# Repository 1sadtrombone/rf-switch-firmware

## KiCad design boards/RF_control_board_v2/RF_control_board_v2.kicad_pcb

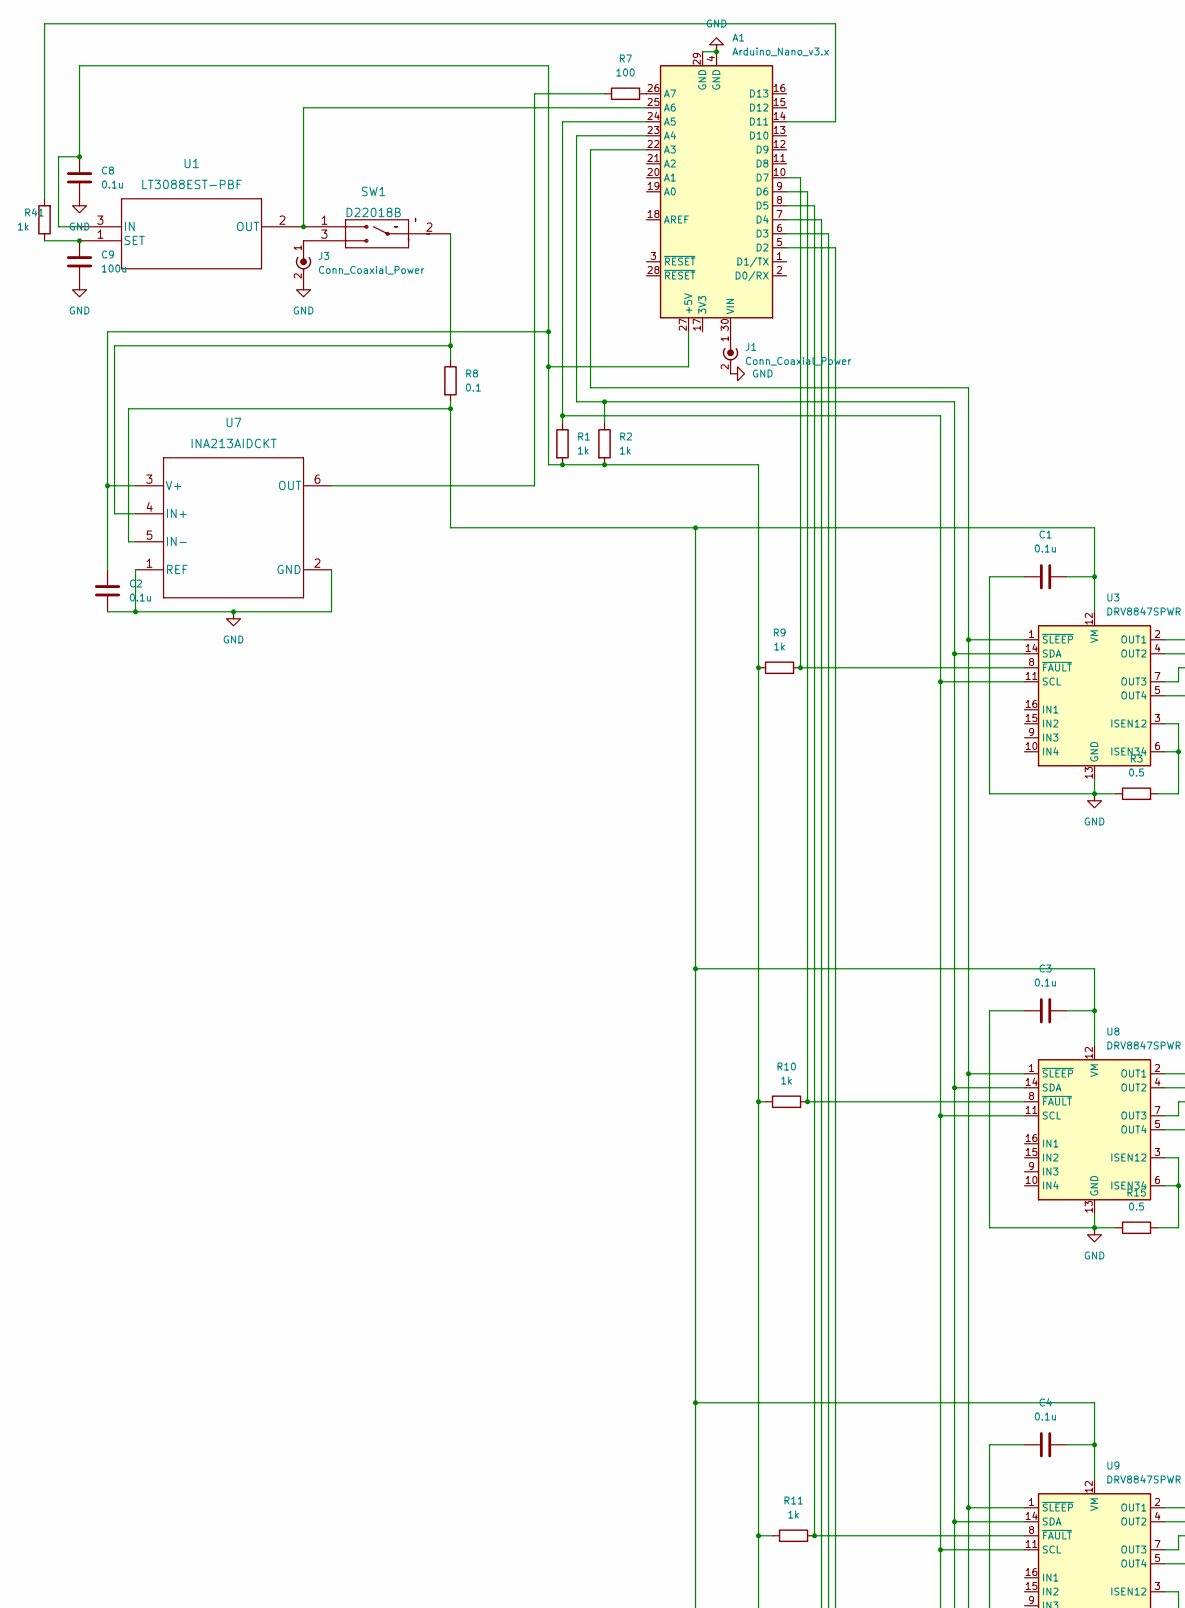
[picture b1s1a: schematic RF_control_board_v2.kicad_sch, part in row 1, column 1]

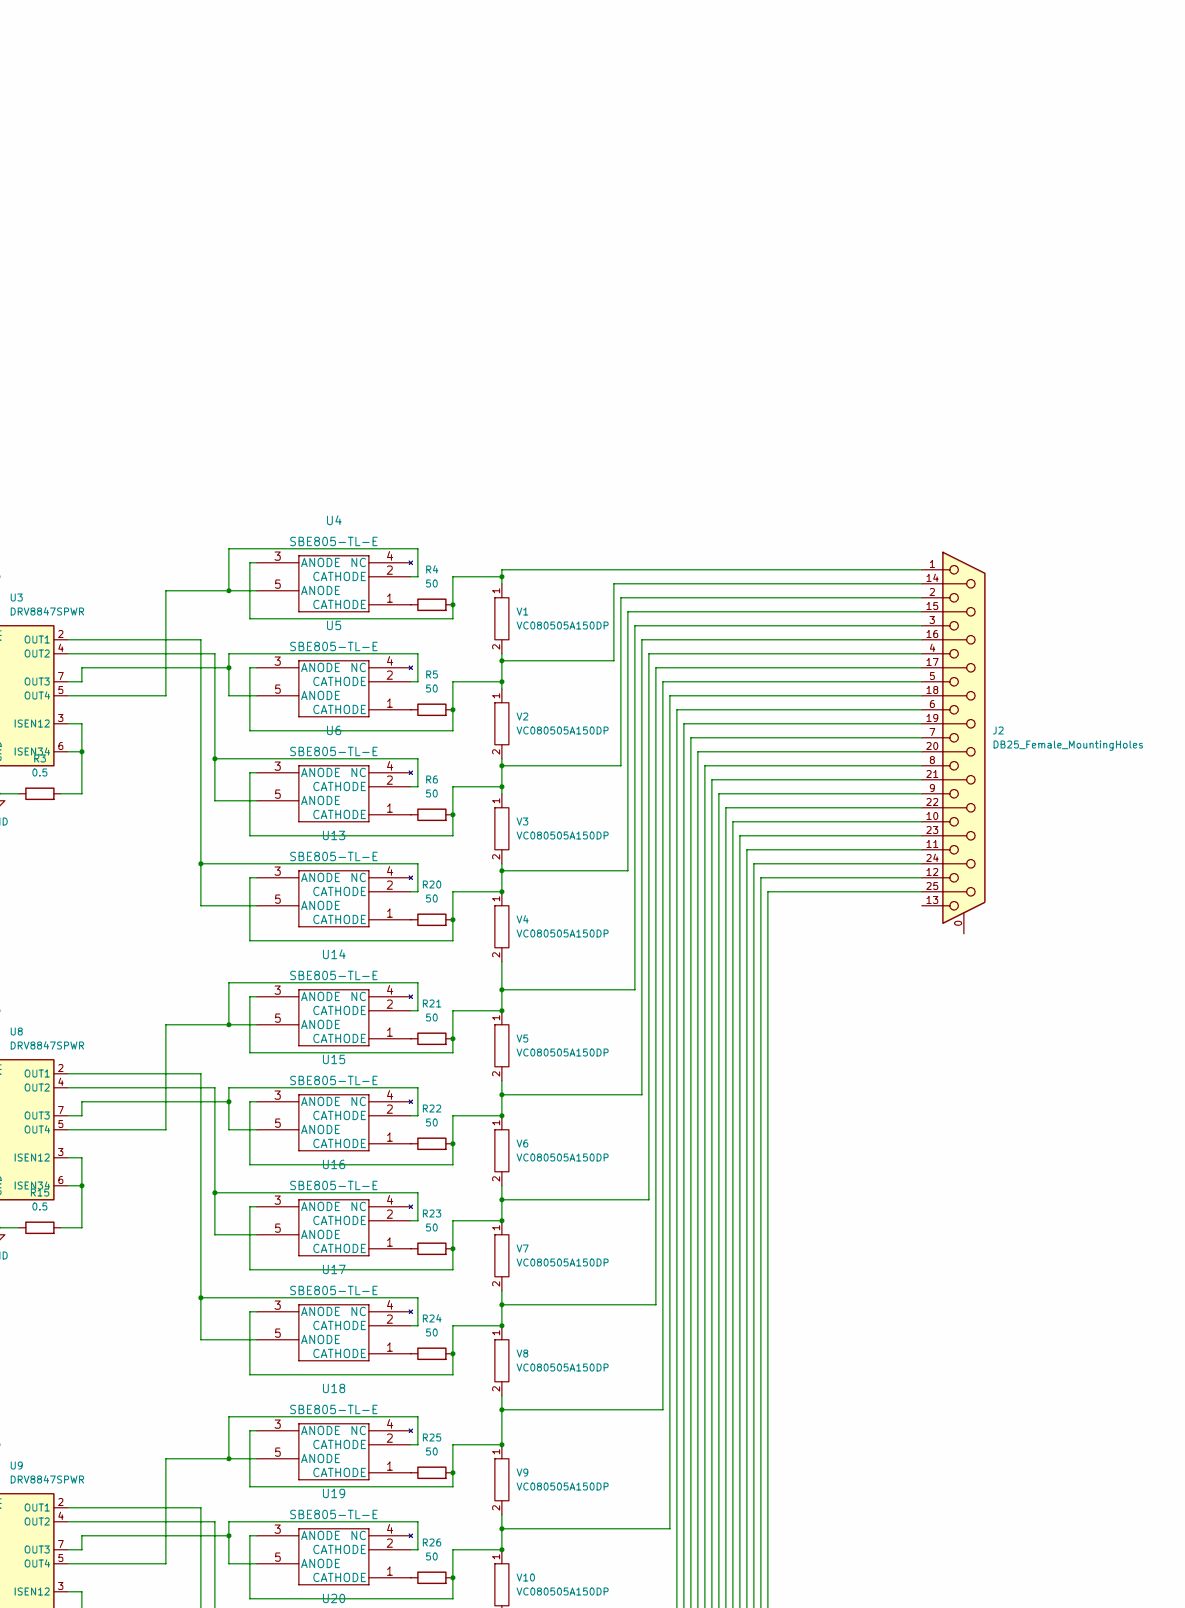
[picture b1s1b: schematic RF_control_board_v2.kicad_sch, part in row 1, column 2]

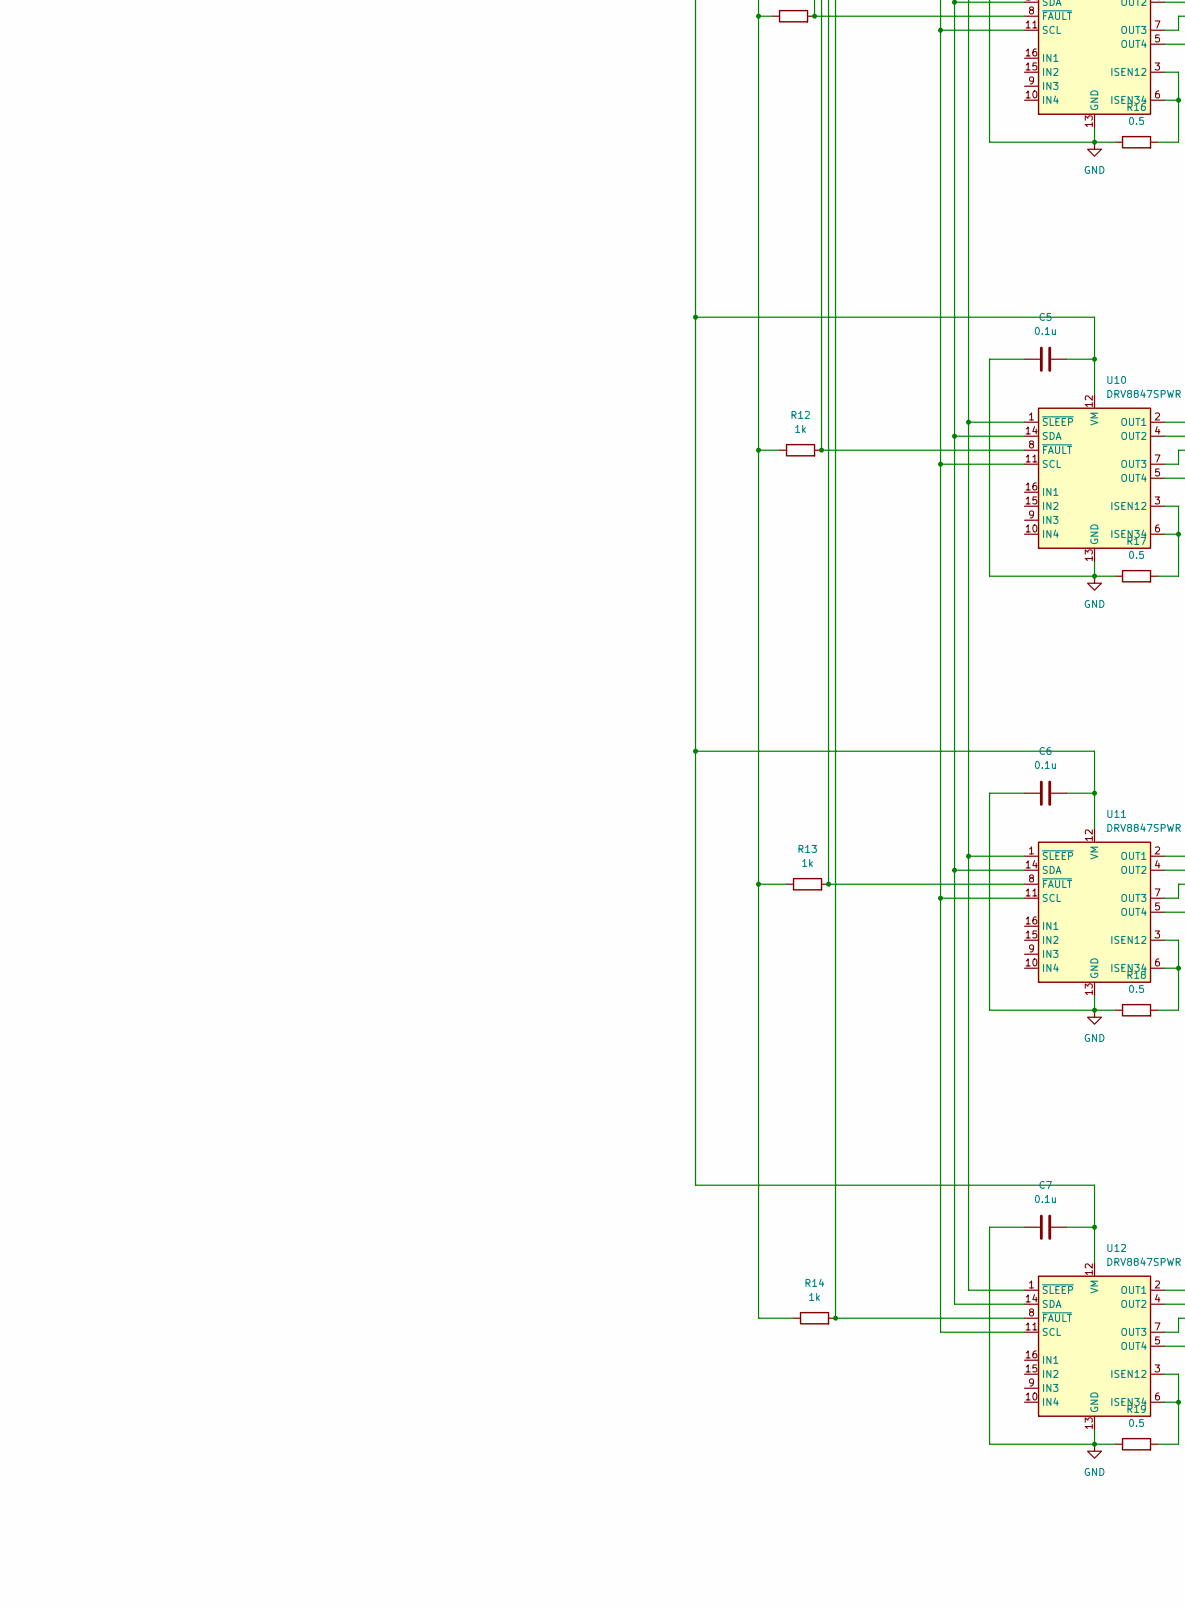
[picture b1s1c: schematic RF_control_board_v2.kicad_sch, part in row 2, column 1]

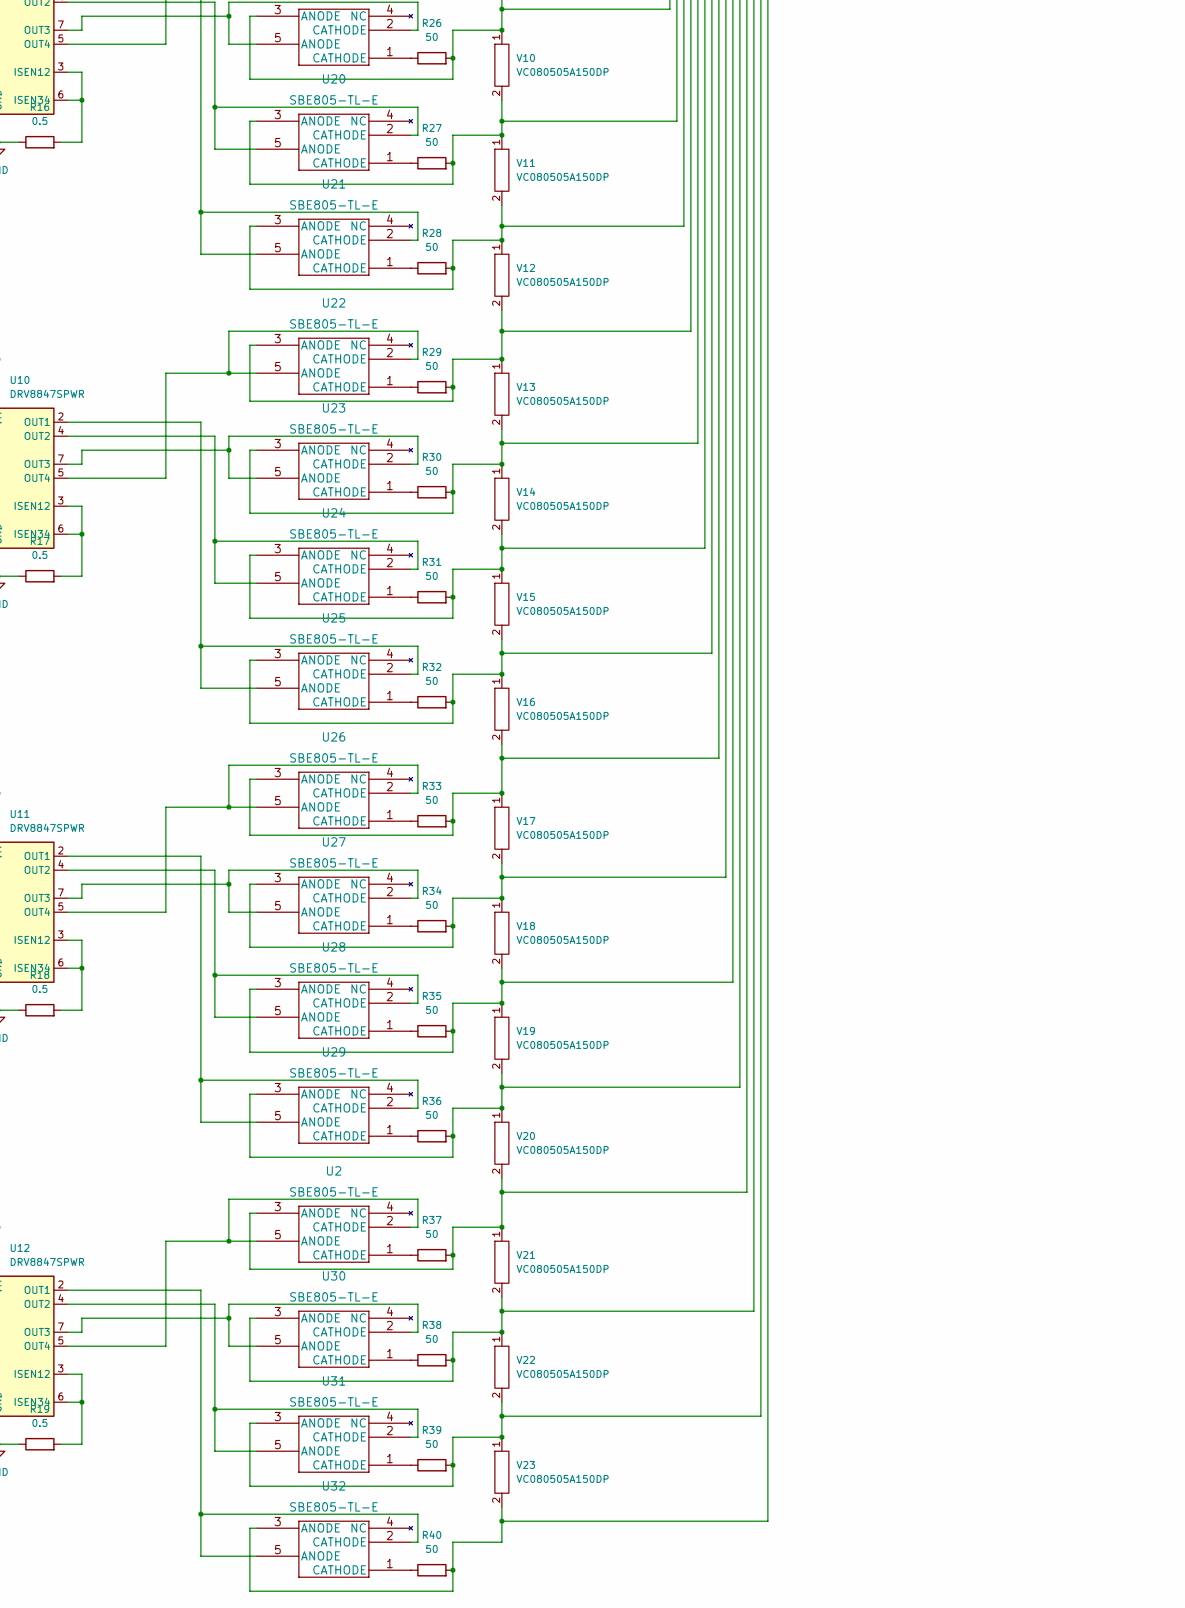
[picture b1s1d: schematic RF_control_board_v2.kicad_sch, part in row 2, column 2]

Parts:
A1: Arduino_Nano_v3.x; Arduino_Nano
C1, C2, C3, C4, C5, C6, C7, C8: 0.1u; C_0603_1608Metric
C9: 100u; C_0603_1608Metric
J1: Conn_Coaxial_Power; BarrelJack_CUI_PJ-063AH_Horizontal
J2: DB25_Female_MountingHoles; DSUB-25_Female_Horizontal_P2.77x2.84mm_EdgePinOffset4.94mm_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
J3: Conn_Coaxial_Power; BNC_Amphenol_B6252HB-NPP3G-50_Horizontal
R1, R2, R9, R10, R11, R12, R13, R14, R41: 1k; R_0603_1608Metric
R3, R15, R16, R17, R18, R19: 0.5; R_0603_1608Metric
R4, R5, R6, R20, R21, R22, R23, R24, R25, R26, R27, R28, R29, R30, R31, R32, R33, R34, R35, R36, R37, R38, R39, R40: 50; R_0603_1608Metric
R7: 100; R_0603_1608Metric
R8: 0.1; R_0603_1608Metric
SW1: D22018B; D22012_B_NKK
U1: LT3088EST-PBF; SOT-223_ST_LIT
U2, U4, U5, U6, U13, U14, U15, U16, U17, U18, U19, U20, U21, U22, U23, U24, U25, U26, U27, U28, U29, U30, U31, U32: SBE805-TL-E; SOT-753_1P6X2P9_ONS
U3, U8, U9, U10, U11, U12: DRV8847SPWR; TSSOP-16_4.4x5mm_P0.65mm
U7: INA213AIDCKT; DCK0006A_N
V1, V2, V3, V4, V5, V6, V7, V8, V9, V10, V11, V12, V13, V14, V15, V16, V17, V18, V19, V20, V21, V22, V23: VC080505A150DP; AVX_0805

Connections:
GND: A1.4 (GND), A1.29 (GND), C1.1, C2.1, C3.1, C4.1, C5.1, C6.1, C7.1, C8.2, C9.2, J1.2 (Ext), J3.2 (Ext), R3.1, R15.1, R16.1, R17.1, R18.1, R19.1, U3.13 (GND), U7.1 (REF), U7.2 (GND), U8.13 (GND), U9.13 (GND), U10.13 (GND), U11.13 (GND), U12.13 (GND)
unnamed: A1.5 (D2), R14.2, U12.8 (~FAULT)
unnamed: A1.6 (D3), R13.2, U11.8 (~FAULT)
unnamed: A1.7 (D4), R12.2, U10.8 (~FAULT)
unnamed: A1.8 (D5), R11.2, U9.8 (~FAULT)
unnamed: A1.9 (D6), R10.2, U8.8 (~FAULT)
unnamed: A1.10 (D7), R9.2, U3.8 (~FAULT)
unnamed: A1.14 (D11), R41.2
unnamed: A1.22 (A3), U3.1 (~SLEEP), U8.1 (~SLEEP), U9.1 (~SLEEP), U10.1 (~SLEEP), U11.1 (~SLEEP), U12.1 (~SLEEP)
unnamed: A1.23 (A4), R2.1, U3.14 (SDA), U8.14 (SDA), U9.14 (SDA), U10.14 (SDA), U11.14 (SDA), U12.14 (SDA)
unnamed: A1.24 (A5), R1.1, U3.11 (SCL), U8.11 (SCL), U9.11 (SCL), U10.11 (SCL), U11.11 (SCL), U12.11 (SCL)
unnamed: A1.25 (A6), SW1.1, U1.2 (OUT)
unnamed: A1.26 (A7), R7.2
unnamed: A1.27 (+5V), C2.2, C8.1, R1.2, R2.2, R9.1, R10.1, R11.1, R12.1, R13.1, R14.1, U1.3 (IN), U7.3 (V+)
unnamed: A1.30 (VIN), J1.1 (In)
unnamed: C1.2, C3.2, C4.2, C5.2, C6.2, C7.2, R8.2, U3.12 (VM), U7.5 (IN-), U8.12 (VM), U9.12 (VM), U10.12 (VM), U11.12 (VM), U12.12 (VM)
unnamed: C9.1, R41.1, U1.1 (SET)
unnamed: J2.1, R4.2, U4.3 (ANODE), V1.1
unnamed: J2.2, R6.2, U6.3 (ANODE), V2.2, V3.1
unnamed: J2.3, R21.2, U14.3 (ANODE), V4.2, V5.1
unnamed: J2.4, R23.2, U16.3 (ANODE), V6.2, V7.1
unnamed: J2.5, R25.2, U18.3 (ANODE), V8.2, V9.1
unnamed: J2.6, R27.2, U20.3 (ANODE), V10.2, V11.1
unnamed: J2.7, R29.2, U22.3 (ANODE), V12.2, V13.1
unnamed: J2.8, R31.2, U24.3 (ANODE), V14.2, V15.1
unnamed: J2.9, R33.2, U26.3 (ANODE), V16.2, V17.1
unnamed: J2.10, R35.2, U28.3 (ANODE), V18.2, V19.1
unnamed: J2.11, R37.2, U2.3 (ANODE), V20.2, V21.1
unnamed: J2.12, R39.2, U31.3 (ANODE), V22.2, V23.1
unnamed: J2.14, R5.2, U5.3 (ANODE), V1.2, V2.1
unnamed: J2.15, R20.2, U13.3 (ANODE), V3.2, V4.1
unnamed: J2.16, R22.2, U15.3 (ANODE), V5.2, V6.1
unnamed: J2.17, R24.2, U17.3 (ANODE), V7.2, V8.1
unnamed: J2.18, R26.2, U19.3 (ANODE), V9.2, V10.1
unnamed: J2.19, R28.2, U21.3 (ANODE), V11.2, V12.1
unnamed: J2.20, R30.2, U23.3 (ANODE), V13.2, V14.1
unnamed: J2.21, R32.2, U25.3 (ANODE), V15.2, V16.1
unnamed: J2.22, R34.2, U27.3 (ANODE), V17.2, V18.1
unnamed: J2.23, R36.2, U29.3 (ANODE), V19.2, V20.1
unnamed: J2.24, R38.2, U30.3 (ANODE), V21.2, V22.1
unnamed: J2.25, R40.2, U32.3 (ANODE), V23.2
unnamed: J3.1 (In), SW1.3
unnamed: R3.2, U3.3 (ISEN12), U3.6 (ISEN34)
unnamed: R4.1, U4.1 (CATHODE)
unnamed: R5.1, U5.1 (CATHODE)
unnamed: R6.1, U6.1 (CATHODE)
unnamed: R7.1, U7.6 (OUT)
unnamed: R8.1, SW1.2, U7.4 (IN+)
unnamed: R15.2, U8.3 (ISEN12), U8.6 (ISEN34)
unnamed: R16.2, U9.3 (ISEN12), U9.6 (ISEN34)
unnamed: R17.2, U10.3 (ISEN12), U10.6 (ISEN34)
unnamed: R18.2, U11.3 (ISEN12), U11.6 (ISEN34)
unnamed: R19.2, U12.3 (ISEN12), U12.6 (ISEN34)
unnamed: R20.1, U13.1 (CATHODE)
unnamed: R21.1, U14.1 (CATHODE)
unnamed: R22.1, U15.1 (CATHODE)
unnamed: R23.1, U16.1 (CATHODE)
unnamed: R24.1, U17.1 (CATHODE)
unnamed: R25.1, U18.1 (CATHODE)
unnamed: R26.1, U19.1 (CATHODE)
unnamed: R27.1, U20.1 (CATHODE)
unnamed: R28.1, U21.1 (CATHODE)
unnamed: R29.1, U22.1 (CATHODE)
unnamed: R30.1, U23.1 (CATHODE)
unnamed: R31.1, U24.1 (CATHODE)
unnamed: R32.1, U25.1 (CATHODE)
unnamed: R33.1, U26.1 (CATHODE)
unnamed: R34.1, U27.1 (CATHODE)
unnamed: R35.1, U28.1 (CATHODE)
unnamed: R36.1, U29.1 (CATHODE)
unnamed: R37.1, U2.1 (CATHODE)
unnamed: R38.1, U30.1 (CATHODE)
unnamed: R39.1, U31.1 (CATHODE)
unnamed: R40.1, U32.1 (CATHODE)
unnamed: U3.4 (OUT2), U6.2 (CATHODE), U6.5 (ANODE)
unnamed: U3.5 (OUT4), U4.2 (CATHODE), U4.5 (ANODE)
unnamed: U3.7 (OUT3), U5.2 (CATHODE), U5.5 (ANODE)
unnamed: U10.2 (OUT1), U25.2 (CATHODE), U25.5 (ANODE)
unnamed: U10.4 (OUT2), U24.2 (CATHODE), U24.5 (ANODE)
unnamed: U10.5 (OUT4), U22.2 (CATHODE), U22.5 (ANODE)
unnamed: U10.7 (OUT3), U23.2 (CATHODE), U23.5 (ANODE)
unnamed: U11.2 (OUT1), U29.2 (CATHODE), U29.5 (ANODE)
unnamed: U11.4 (OUT2), U28.2 (CATHODE), U28.5 (ANODE)
unnamed: U11.5 (OUT4), U26.2 (CATHODE), U26.5 (ANODE)
unnamed: U11.7 (OUT3), U27.2 (CATHODE), U27.5 (ANODE)
unnamed: U12.2 (OUT1), U32.2 (CATHODE), U32.5 (ANODE)
unnamed: U12.4 (OUT2), U31.2 (CATHODE), U31.5 (ANODE)
unnamed: U2.2 (CATHODE), U2.5 (ANODE), U12.5 (OUT4)
unnamed: U12.7 (OUT3), U30.2 (CATHODE), U30.5 (ANODE)
unnamed: U3.2 (OUT1), U13.2 (CATHODE), U13.5 (ANODE)
unnamed: U8.5 (OUT4), U14.2 (CATHODE), U14.5 (ANODE)
unnamed: U8.7 (OUT3), U15.2 (CATHODE), U15.5 (ANODE)
unnamed: U8.4 (OUT2), U16.2 (CATHODE), U16.5 (ANODE)
unnamed: U8.2 (OUT1), U17.2 (CATHODE), U17.5 (ANODE)
unnamed: U9.5 (OUT4), U18.2 (CATHODE), U18.5 (ANODE)
unnamed: U9.7 (OUT3), U19.2 (CATHODE), U19.5 (ANODE)
unnamed: U9.4 (OUT2), U20.2 (CATHODE), U20.5 (ANODE)
unnamed: U9.2 (OUT1), U21.2 (CATHODE), U21.5 (ANODE)

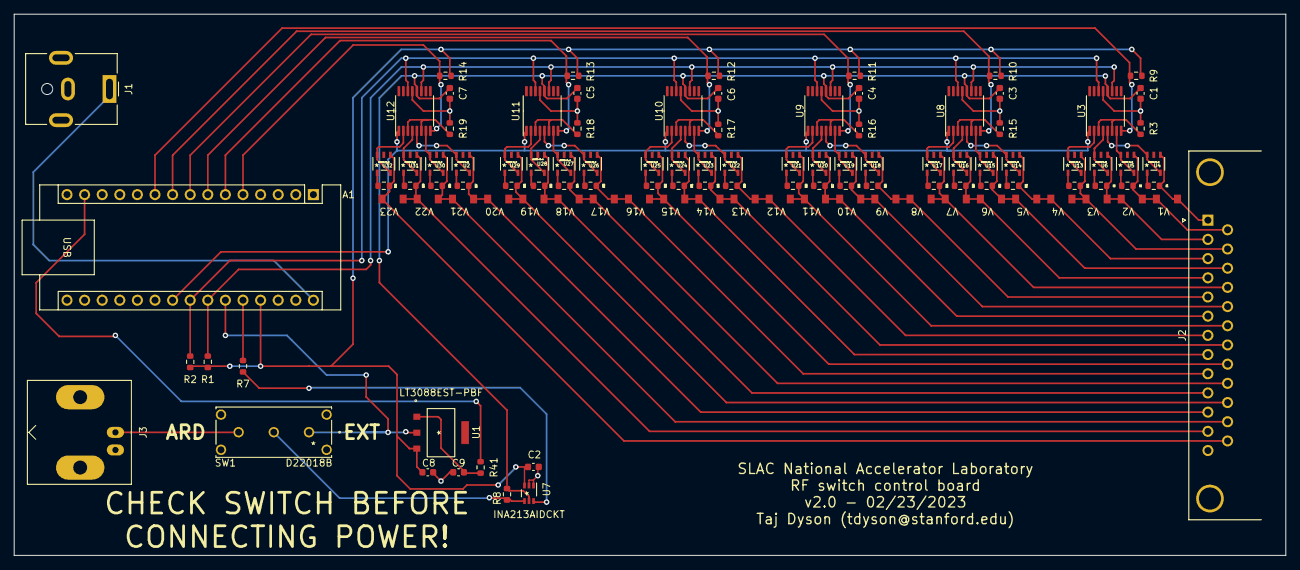
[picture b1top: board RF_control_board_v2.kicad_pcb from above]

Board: 2 copper layers, 183.5 x 78.1 mm, 110 parts (0 on the bottom side), 98 nets.

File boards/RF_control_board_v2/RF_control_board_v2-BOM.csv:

Id,Designator,Package,Quantity,Designation,Supplier and ref,Column1,_1
1,U7,DCK0006A_N,1,INA213AIDCKT,,,
2,U1,SOT-223_ST_LIT,1,LT3088EST-PBF,,,
3,"R2,R1,R14,R13,R12,R11,R10,R9,R41",R_0603_1608Metric,9,1k,,,
4,R8,R_0603_1608Metric,1,0.1,,,
5,"R19,R18,R3,R15,R16,R17",R_0603_1608Metric,6,0.5,,,
6,"U32,U13,U19,U26,U4,U15,U24,U31,U29,U30,U21,U20,U23,U6,U27,U22,U14,U28,U2,U17,U5,U16,U25,U18",SOT-753_1P6X2P9_ONS,24,SBE805-TL-E,,,
7,"R36,R22,R24,R20,R35,R37,R29,R40,R38,R4,R39,R23,R21,R34,R32,R25,R26,R6,R31,R27,R33,R28,R30,R5",R_0603_1608Metric,24,50,,,
8,"U8,U10,U3,U9,U12,U11",TSSOP-16_4.4x5mm_P0.65mm,6,DRV8847SPWR,,,
9,"C7,C5,C8,C3,C2,C4,C1,C6",C_0603_1608Metric,8,0.1u,,,
10,"V3,V1,V15,V13,V2,V20,V18,V14,V6,V23,V12,V8,V7,V10,V16,V11,V19,V17,V21,V22,V9,V5,V4",AVX_0805,23,VC080505A150DP,,,
11,J2,DSUB-25_Female_Horizontal_P2.77x2.84mm_EdgePinOffset4.94mm_Housed_MountingHolesOffset7.48mm,1,DB25_Female_MountingHoles,,,
12,C9,C_0603_1608Metric,1,10u,,,
13,A1,Arduino_Nano,1,Arduino_Nano_v3.x,,,
14,R7,R_0603_1608Metric,1,100,,,
15,SW1,D22012_B_NKK,1,D22018B,,,
16,J3,BNC_Amphenol_B6252HB-NPP3G-50_Horizontal,1,Conn_Coaxial_Power,,,
17,J1,BarrelJack_CUI_PJ-063AH_Horizontal,1,Conn_Coaxial_Power,,,

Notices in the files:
parts and their libraries:
Copyright 2021 Accelerated Designs. All rights reserved.
